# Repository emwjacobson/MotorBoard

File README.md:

# MotorBoard

Goals for this project:

- Integreate ESP32
- Control up to 3 stepper motors
  - Shared pins:
    - MS1, MS2, MS3, Reset, Enable
  - Unique pins per stepper:
    - Sleep, Step, Dir
  - Total of 5 + 3(3) = 14 pins to control 3 steppers.
- Control up to 2 "hobby" servos
- 6 digital inputs
  - Limit switches, User IO (Buttons)

Decisions that need to be made:
- How will it be powered?
  - Barrel Jack? Screw Terminals?
  - Stepper motors will run off 8-35V, so 12V input should be good
- Stepper Connector
  - Leaning towards screw terminals, as they seem pretty universal
  - Could also use 4/6-pin JST connector
- Should step resolution be software controlled, or have jumpers on PCB?

Components:
- [Stepper Driver](https://www.lcsc.com/product-detail/Motor-Driver-ICs_Allegro-MicroSystems-LLC-A4988SETTR-T_C38437.html)
- [ESP32 Module](https://www.lcsc.com/product-detail/WiFi-Modules_Espressif-Systems-ESP32-WROVER-IE-8MB_C2934565.html)
  - The IE(8MB) seems to be the cheapest in the WROVER-IE series. The 4MB and 16MB variants are also supported, though seem slightly more expensive on LCSC
  - The WROVER-E series is also supported. The only difference between the two is the resistor connecting the antenna output either to the PCB antenna, or the external antenna. The -E model attaches to the PCB antenna, and the -IE model attaches to the external antenna.

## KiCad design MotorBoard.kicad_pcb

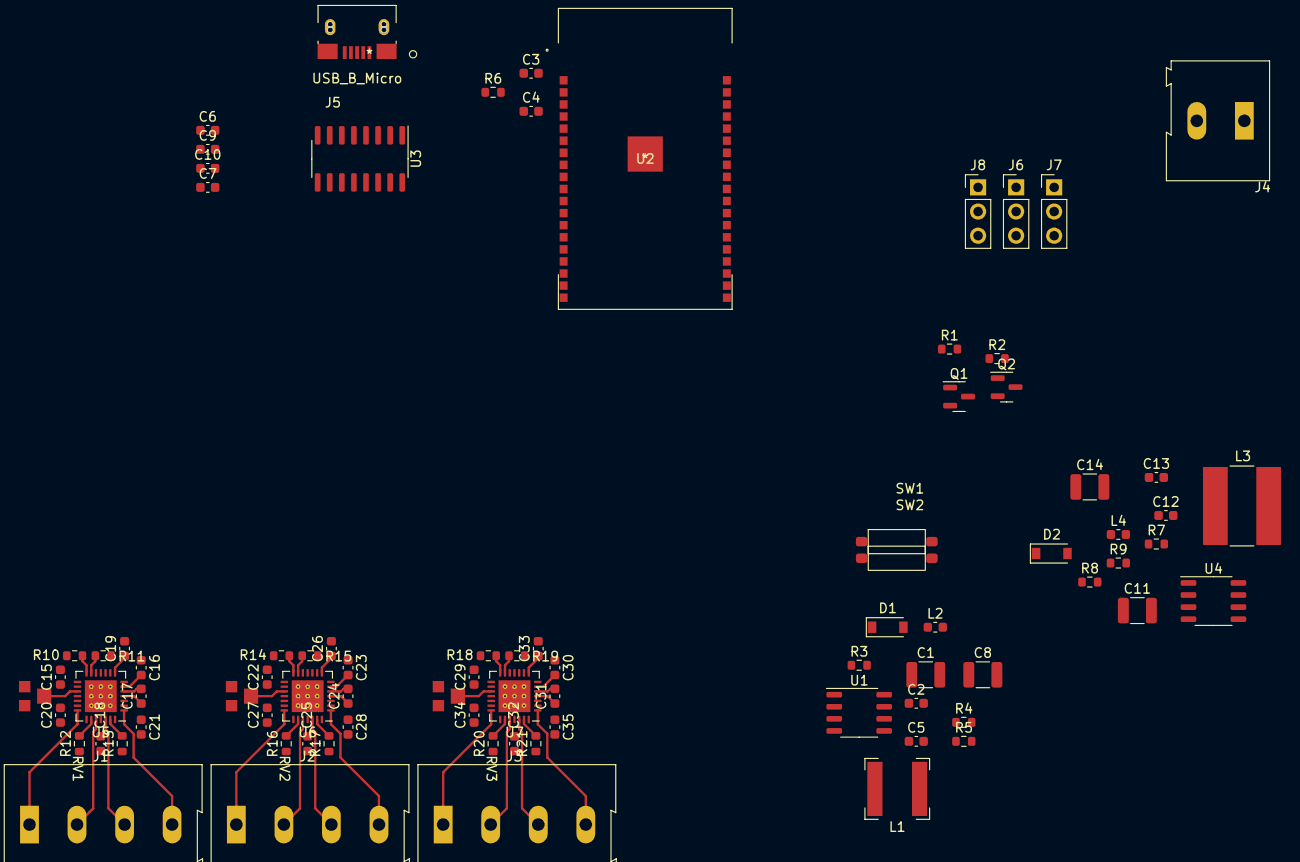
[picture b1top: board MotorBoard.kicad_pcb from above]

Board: 4 copper layers, 84 parts (0 on the bottom side), 79 nets.

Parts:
C1, C8, C11, C14: 100uF; C_1210_3225Metric
C2: 150pF; C_0603_1608Metric
C3: 22uF; C_0603_1608Metric
C4, C7, C9, C10, C16, C17, C20, C21, C23, C24, C27, C28, C30, C31, C34, C35: 100nF; C_0603_1608Metric
C5, C6, C13: 10uF; C_0603_1608Metric
C12: 200pF; C_0603_1608Metric
C15, C19, C22, C26, C29, C33: 220nF; C_0603_1608Metric
C18, C25, C32: 4.7uF; C_0603_1608Metric
D1, D2: 1N5819; D_SOD-123
J1, J2, J3: Screw_Terminal_01x04; TerminalBlock_Altech_AK300-4_P5.00mm
J4: Screw_Terminal_01x02; TerminalBlock_Altech_AK300-2_P5.00mm
J5: USB_B_Micro; U254-051T-4BH83-S1S
J6, J7, J8: Conn_01x03; PinHeader_1x03_P2.54mm_Vertical
L1: 33uH; L_Bourns-SRN6028
L2, L4: 1uH; L_0603_1608Metric
L3: 47uH; L_Bourns-SRN8040_8x8.15mm
Q1, Q2: Q_NPN_BEC; SOT-23
R1, R2, R6, R11, R15, R19: 10k; R_0603_1608Metric
R3: 0.39; R_0603_1608Metric
R4: 18k; R_0603_1608Metric
R5: 11k; R_0603_1608Metric
R7: 0.5; R_0603_1608Metric
R8: 3k; R_0603_1608Metric
R9: 1k; R_0603_1608Metric
R10, R14, R18: 100k; R_0603_1608Metric
R12, R13, R16, R17, R20, R21: 0.05; R_0603_1608Metric
RV1, RV2, RV3: 4.7k; VG039NCHXTB472
SW1, SW2: SW_SPST; TS-1101-C-W
U1, U4: MC34063AD; SOP-8_3.9x4.9mm_P1.27mm
U2: ESP32-WROVER-E; ESP32-WROVER-IE
U3: CH340C; SOIC-16_3.9x9.9mm_P1.27mm
U5, U6, U7: A4988SETTR-T; QFN-28-1EP_5x5mm_P0.5mm_EP3.35x3.35mm_ThermalVias

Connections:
3v3: C3.1, C4.1, C8.1, L2.2, Q1.3 (C), R6.1, SW1.1 (A), U2.2 (3V3)
5v: C14.1, C15.1, C22.1, C29.1, J6.1, J7.1, J8.1, L4.2, R10.2, R14.2, R18.2, RV1.1, RV2.1, RV3.1, U5.15 (VDD), U6.15 (VDD), U7.15 (VDD)
12v: C1.1, C11.1, C16.1, C18.1, C20.1, C21.1, C23.1, C25.1, C27.1, C28.1, C30.1, C32.1, C34.1, C35.1, J4.1, R3.1, R7.1, U1.6 (Vin), U4.6 (Vin), U5.22 (VBB1), U5.28 (VBB2), U6.22 (VBB1), U6.28 (VBB2), U7.22 (VBB1), U7.28 (VBB2)
/BOOT: Q2.3 (C), SW2.1 (A), U2.25 (IO0)
/DTR: Q1.2 (E), R2.1, U3.14 (~RTS)
/ESP_RX: U2.34 (RXD0), U3.2 (TXD)
/ESP_TX: U2.35 (TXD0), U3.3 (RXD)
/RTS: Q2.2 (E), R1.1, U3.13 (~DTR)
/SERVO1: J7.2, U2.11 (IO26)
/SERVO2: J8.2, U2.12 (IO27)
/SERVO3: J6.2, U2.13 (IO14)
/ST1_1A: J1.2, U5.24 (OUT1A)
/ST1_1B: J1.1, U5.21 (OUT1B)
/ST1_2A: J1.3, U5.26 (OUT2A)
/ST1_2B: J1.4, U5.1 (OUT2B)
/ST1_DIR: U2.26 (IO4), U5.19 (DIR)
/ST1_STEP: U2.29 (IO5), U5.16 (STEP)
/ST2_1A: J2.2, U6.24 (OUT1A)
/ST2_1B: J2.1, U6.21 (OUT1B)
/ST2_2A: J2.3, U6.26 (OUT2A)
/ST2_2B: J2.4, U6.1 (OUT2B)
/ST2_DIR: U2.23 (IO15), U6.19 (DIR)
/ST2_STEP: U2.24 (IO2), U6.16 (STEP)
/ST3_1A: J3.2, U7.24 (OUT1A)
/ST3_1B: J3.1, U7.21 (OUT1B)
/ST3_2A: J3.3, U7.26 (OUT2A)
/ST3_2B: J3.4, U7.1 (OUT2B)
/ST3_DIR: U2.14 (IO12), U7.19 (DIR)
/ST3_STEP: U2.16 (IO13), U7.16 (STEP)
/ST_Enable: U2.31 (IO19), U5.2 (~ENABLE), U6.2 (~ENABLE), U7.2 (~ENABLE)
/ST_MS1: U2.37 (IO23), U5.9 (MS1), U6.9 (MS1), U7.9 (MS1)
/ST_MS2: U2.36 (IO22), U5.10 (MS2), U6.10 (MS2), U7.10 (MS2)
/ST_MS3: U2.33 (IO21), U5.11 (MS3), U6.11 (MS3), U7.11 (MS3)
/ST_Reset: U2.30 (IO18), U5.12 (RESET), U6.12 (RESET), U7.12 (RESET)
/USB_5v: C6.1, C7.1, C9.1, J5.1 (VBUS), U3.16 (VCC)
/USB_D+: J5.3 (D+), U3.5 (UD+)
/USB_D-: J5.2 (D-), U3.6 (UD-)
GND: C1.2, C2.2, C3.2, C4.2, C5.2, C6.2, C7.2, C8.2, C9.2, C10.2, C11.2, C12.2, C13.2, C14.2, C15.2, C18.2, C19.2, C20.2, C21.2, C22.2, C25.2, C26.2, C27.2, C28.2, C29.2, C32.2, C33.2, C34.2, C35.2, D1.2 (A), D2.2 (A), J4.2, J5.5 (GND), J6.3, J7.3, J8.3, R5.2, R9.2, R11.2, R12.1, R13.1, R15.2, R16.1, R17.1, R19.2, R20.1, R21.1, RV1.3, RV2.3, RV3.3, SW1.2 (B), SW2.2 (B), U1.4 (GND), U2.1 (GND), U2.15 (GND), U2.38 (GND), U2.39 (GND), U3.1 (GND), U4.4 (GND), U5.3 (GND), U5.18 (GND), U5.29 (GND), U6.3 (GND), U6.18 (GND), U6.29 (GND), U7.3 (GND), U7.18 (GND), U7.29 (GND)
unnamed: C2.1, U1.3 (TC)
unnamed: C5.1, L1.2, L2.1, R4.1
unnamed: C10.1, U3.4 (V3)
unnamed: C12.1, U4.3 (TC)
unnamed: C13.1, L3.2, L4.1, R8.1
unnamed: C16.2, U5.6 (VCP)
unnamed: C17.1, U5.4 (CP1)
unnamed: C17.2, U5.5 (CP2)
unnamed: C19.1, U5.8 (VREG)
unnamed: C23.2, U6.6 (VCP)
unnamed: C24.1, U6.4 (CP1)
unnamed: C24.2, U6.5 (CP2)
unnamed: C26.1, U6.8 (VREG)
unnamed: C30.2, U7.6 (VCP)
unnamed: C31.1, U7.4 (CP1)
unnamed: C31.2, U7.5 (CP2)
unnamed: C33.1, U7.8 (VREG)
unnamed: D1.1 (K), L1.1, U1.2 (SwE)
unnamed: D2.1 (K), L3.1, U4.2 (SwE)
unnamed: Q1.1 (B), R1.2
unnamed: Q2.1 (B), R2.2
unnamed: R3.2, U1.1 (SwC), U1.7 (Ipk), U1.8 (DC)
unnamed: R4.2, R5.1, U1.5 (Vfb)
unnamed: R6.2, U2.3 (EN)
unnamed: R7.2, U4.1 (SwC), U4.7 (Ipk), U4.8 (DC)
unnamed: R8.2, R9.1, U4.5 (Vfb)
unnamed: R10.1, U5.14 (~SLEEP)
unnamed: R11.1, U5.13 (ROSC)
unnamed: R12.2, U5.23 (SENSE1)
unnamed: R13.2, U5.27 (SENSE2)
unnamed: R14.1, U6.14 (~SLEEP)
unnamed: R15.1, U6.13 (ROSC)
unnamed: R16.2, U6.23 (SENSE1)
unnamed: R17.2, U6.27 (SENSE2)
unnamed: R18.1, U7.14 (~SLEEP)
unnamed: R19.1, U7.13 (ROSC)
unnamed: R20.2, U7.23 (SENSE1)
unnamed: R21.2, U7.27 (SENSE2)
unnamed: RV1.2, U5.17 (VREF)
unnamed: RV2.2, U6.17 (VREF)
unnamed: RV3.2, U7.17 (VREF)

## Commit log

2022-02-05 Began work on schematic
2022-02-05 Wired stepper driver and power supply section
2022-02-06 Broke stepper drivers into hierarchial sheets
2022-02-06 Added part numbers to majority of components
2022-02-06 Started assigning footprints
2022-02-06 Added servo headers
2022-02-07 Began work on PCB layout
